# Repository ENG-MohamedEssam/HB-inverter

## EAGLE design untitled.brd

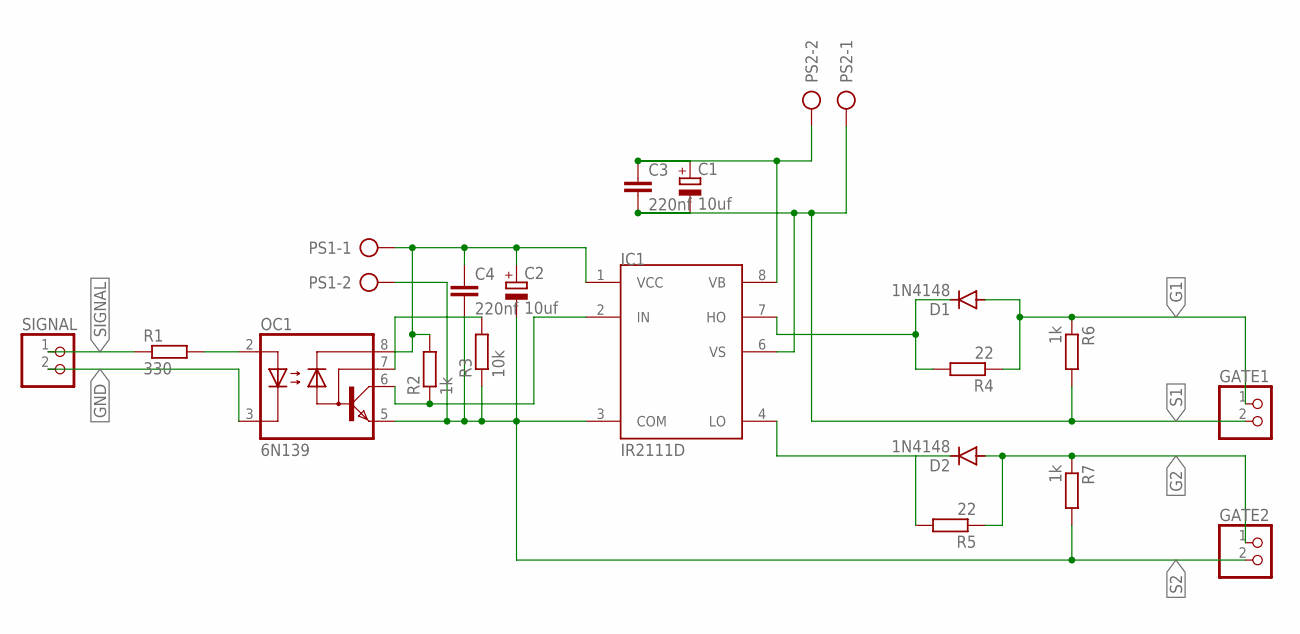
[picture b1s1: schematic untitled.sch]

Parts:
C1, C2: 10uf; E2,5-6E
C3, C4: 220nf; C025-025X050
D1, D2: 1N4148; DO35-10
GATE1, GATE2: PINHD-1X2; 1X02
IC1: IR2111D; DIL08
OC1: 6N139; DIL08
PS1, PS2: AK300/2
R1: 330; 0204/7
R2, R6, R7: 1k; 0204/7
R3: 10k; 0204/7
R4, R5: 22; 0204/7
SIGNAL: PINHD-1X2; 1X02

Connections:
G1: D1.A, GATE1.1, R4.1, R6.1
G2: D2.A, GATE2.1, R5.1, R7.1
GND: OC1.3 (C), SIGNAL.2
unnamed: OC1.2 (A), R1.2
unnamed: OC1.7 (VB), R3.2
unnamed: D1.C, IC1.7 (HO), R4.2
unnamed: IC1.2 (IN), OC1.6 (VO), R2.1
unnamed: D2.C, IC1.4 (LO), R5.2
S1: C1.-, C3.2, GATE1.2, IC1.6 (VS), PS2.1, R6.2
S2: C2.-, C4.2, GATE2.2, IC1.3 (COM), OC1.5 (GND), PS1.2, R3.1, R7.2
SIGNAL: R1.1, SIGNAL.1
VB: C1.+, C3.1, IC1.8 (VB), PS2.2
VCC: C2.+, C4.1, IC1.1 (VCC), OC1.8 (VCC), PS1.1, R2.2

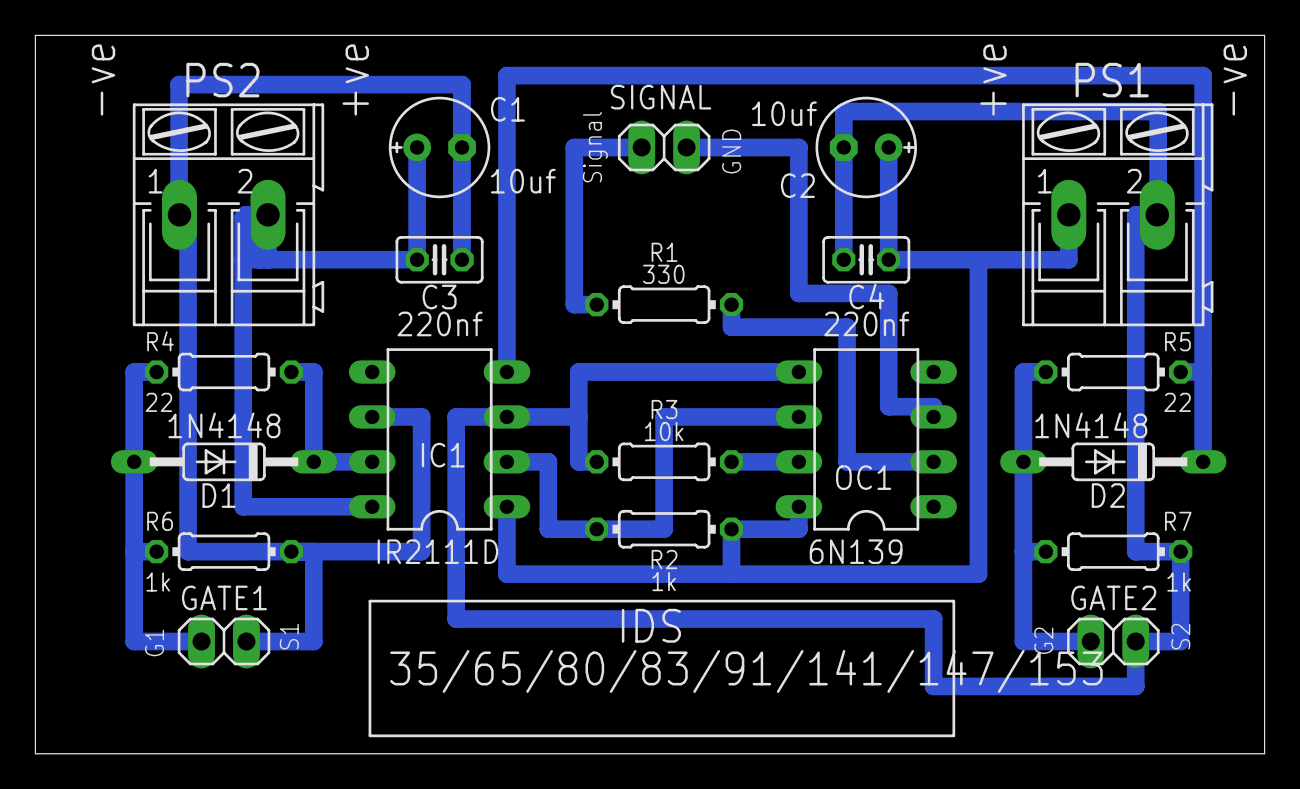
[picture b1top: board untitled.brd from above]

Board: 2 copper layers, 69.5 x 40.6 mm, 20 parts (0 on the bottom side), 13 nets.

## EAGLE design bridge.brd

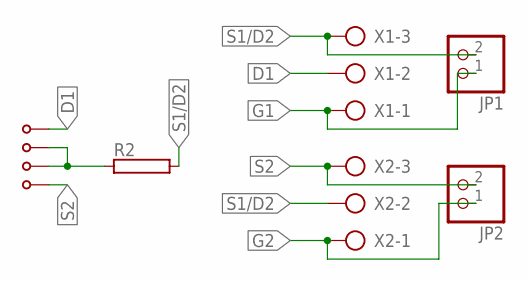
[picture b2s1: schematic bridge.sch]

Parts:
JP1, JP2: PINHD-1X2; 1X02
R2: RKH216-8; KH216-8
U$1, U$2, U$3, U$4: BANANA-JACK; BANANA-PRINT
X1, X2: AK300/3

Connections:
D1: U$1.P$1, X1.2
G1: JP1.1, X1.1
G2: JP2.1, X2.1
unnamed: R2.1, U$2.P$1, U$3.P$1
S1/D2: JP1.2, R2.2, X1.3, X2.2
S2: JP2.2, U$4.P$1, X2.3

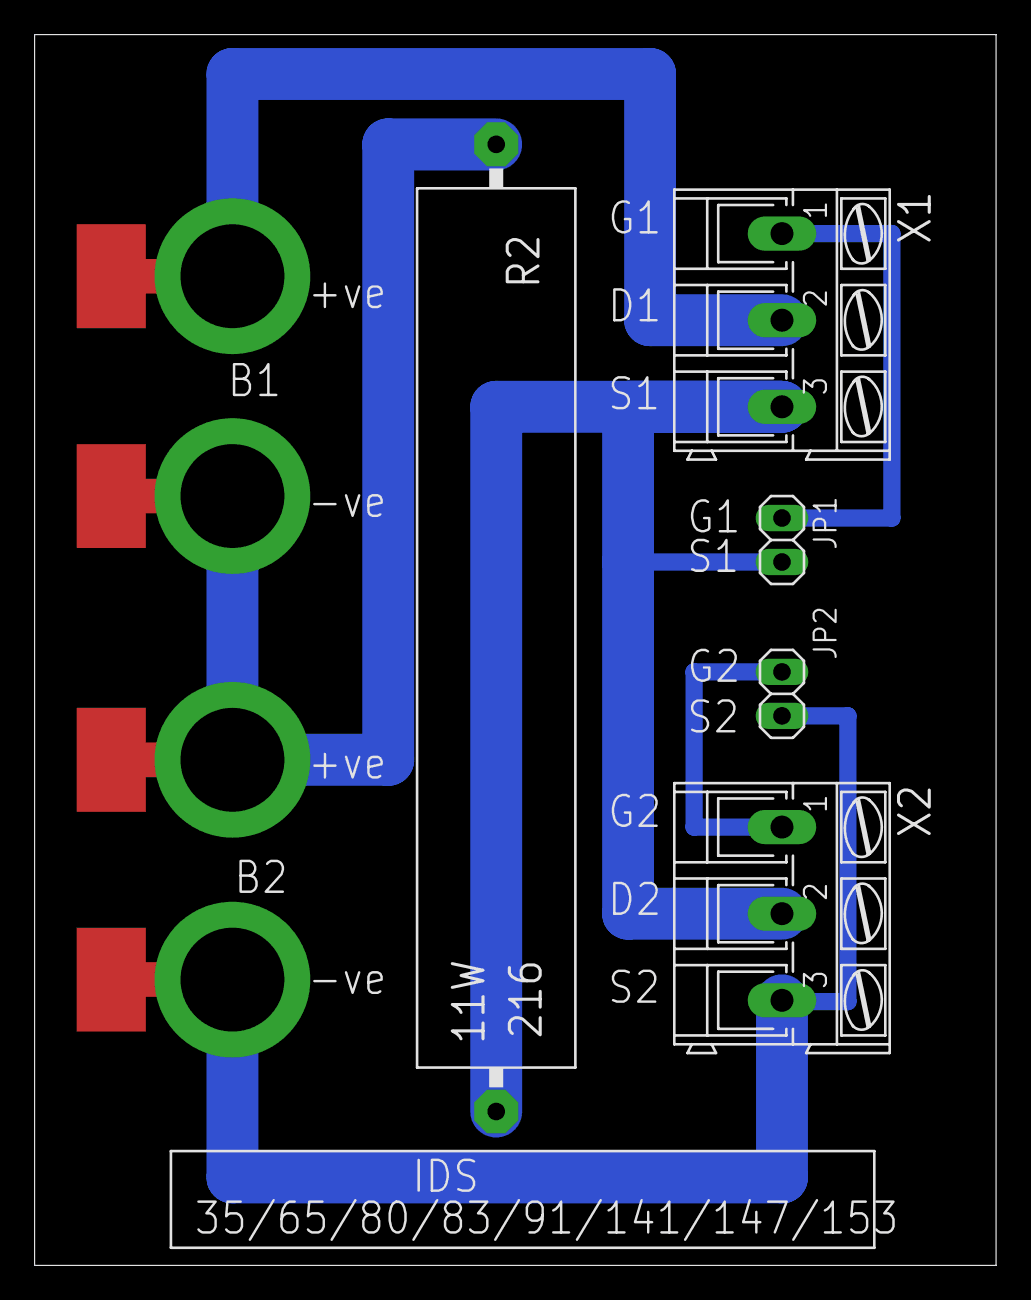
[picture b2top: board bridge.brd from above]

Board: 2 copper layers, 55.6 x 71.1 mm, 9 parts (0 on the bottom side), 6 nets.
